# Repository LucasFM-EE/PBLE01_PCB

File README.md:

# PBLE01_PCB

Project designed for the discipline: Project Based Learning 01.

# Requirements
In this project, the board must match these requirements: 

### 1. Power Supply: 
- Support voltage input of 7V to 12V (DC);
- Provide regulated output of 5V;
- Use a LED to indicate that the board is powered.

### 2. Processing:
- Use a PIC18F4550 as a unit of processing and control;
- Use a pin header compatible with the ICSP standard, to program the microcontroller;
- Use a push-button to reset the microcontroller.

### 3. User interaction:
- Have a keyboard, composed by 5 push-buttons;
- Have a LCD display, which its luminosity is controlled by a trimmer;
- Have at least 4 LED's, which are able to signalize different states of the MCU;
- Have a potentiometer, which is used to provide analog data.

### 4. Peripherals
- Use a Real-Time Clock(RTC) - MCP7940;
- Contain 2 pairs of differential analog inputs(4 analog inputs). Each pair must provide a signal between 0V and 3V for the microcontroller; 
- Contain a analog output, made by a PWM signal;
- Contain a pin header that has the reference signal(GND), the power supply signal(VCC) and the microcontroller pins that aren't being used.

### 5. Communication
- Use a USB-Serial converter(MCP2200), to allow serial communication with the board.

# Functional Diagram
The following image shows a functional diagram of the board: 

# Board sections 
The following image shows the board, divided by the sections mentioned above:

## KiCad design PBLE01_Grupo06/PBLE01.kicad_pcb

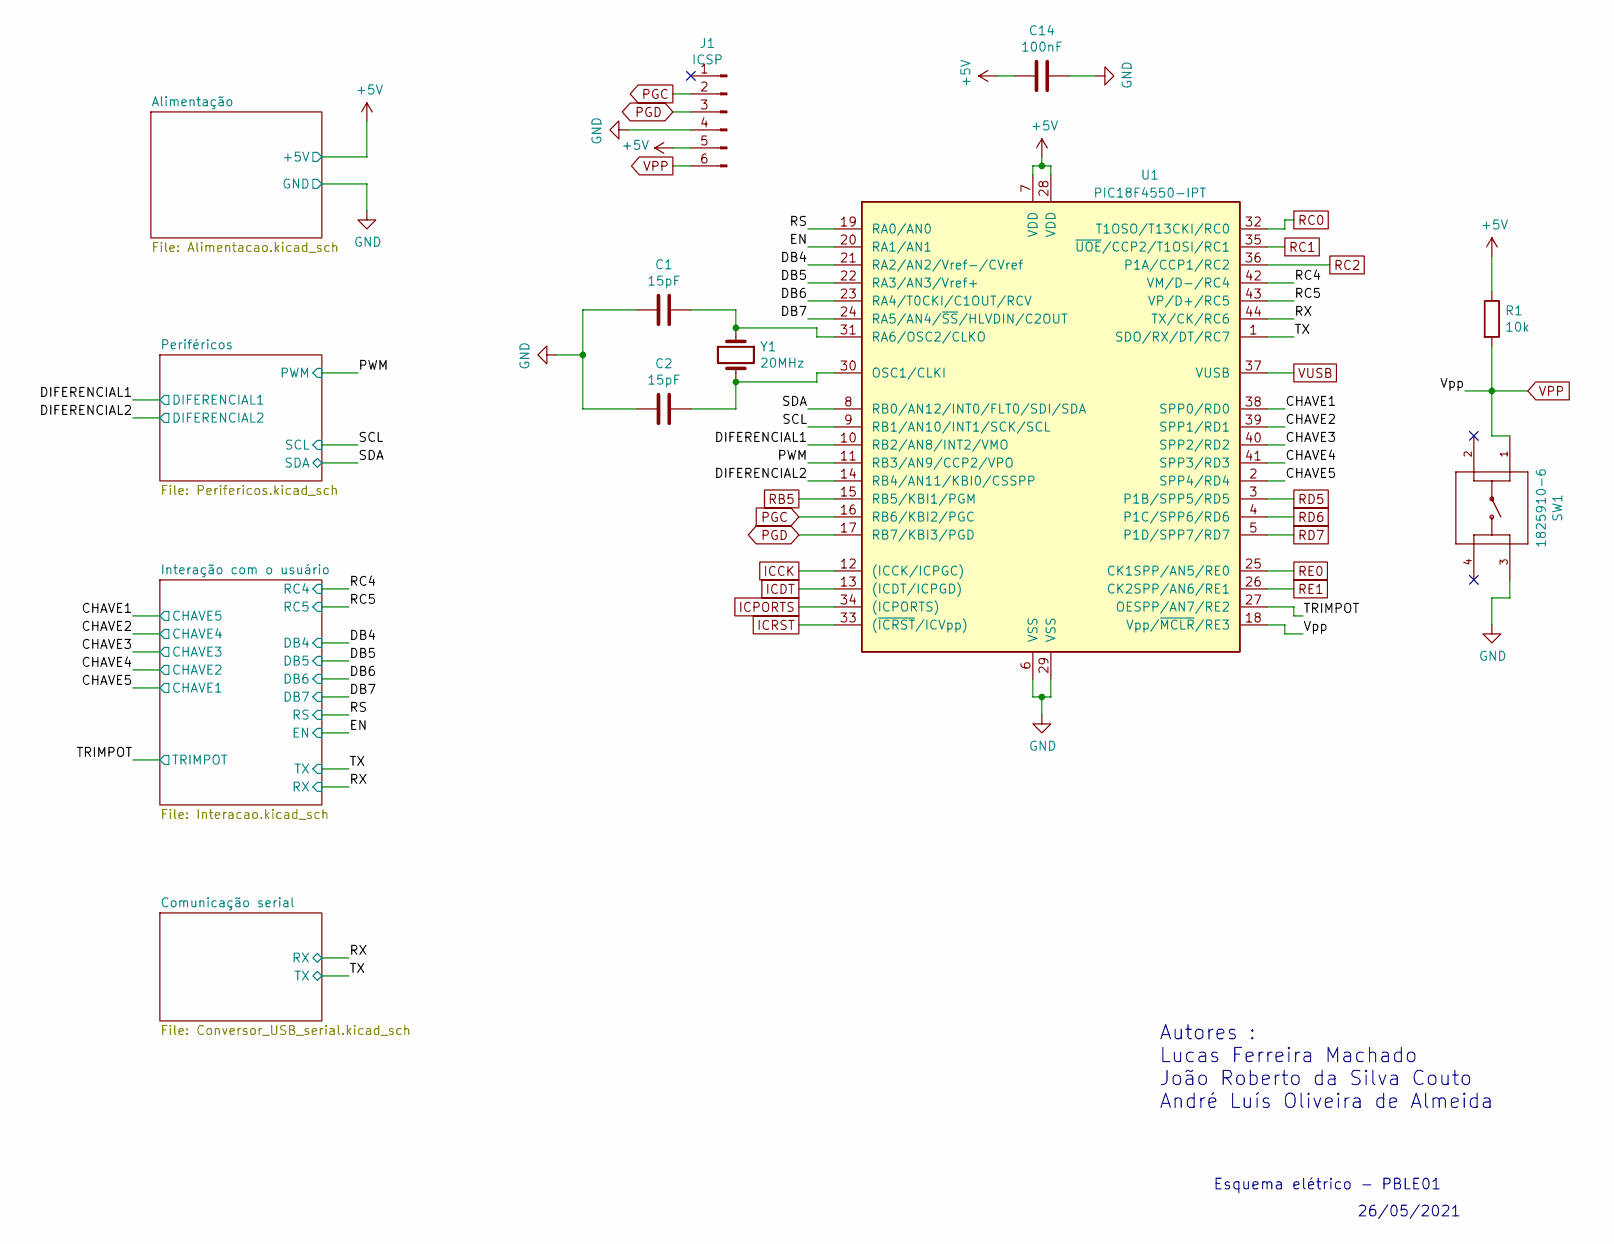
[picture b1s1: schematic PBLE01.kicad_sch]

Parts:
C1, C2: 15pF; C_0805_2012Metric_Pad1.18x1.45mm_HandSolder
C14: 100nF; C_0805_2012Metric_Pad1.18x1.45mm_HandSolder
J1: ICSP; PinHeader_1x06_P2.54mm_Vertical
R1: 10k; R_0805_2012Metric_Pad1.20x1.40mm_HandSolder
SW1: 1825910-6; SW_1825910-6-4
U1: PIC18F4550-IPT; TQFP-44_10x10mm_P0.8mm
Y1: 20MHz; Crystal_HC49-4H_Vertical

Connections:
+5V: C14.1, J1.5, R1.1, U1.7 (VDD), U1.28 (VDD); also elsewhere on the board
/CHAVE1: U1.38 (SPP0/RD0); also elsewhere on the board
/CHAVE2: U1.39 (SPP1/RD1); also elsewhere on the board
/CHAVE3: U1.40 (SPP2/RD2); also elsewhere on the board
/CHAVE4: U1.41 (SPP3/RD3); also elsewhere on the board
/CHAVE5: U1.2 (SPP4/RD4); also elsewhere on the board
/DB4: U1.21 (RA2/AN2/Vref-/CVref); also elsewhere on the board
/DB5: U1.22 (RA3/AN3/Vref+); also elsewhere on the board
/DB6: U1.23 (RA4/T0CKI/C1OUT/RCV); also elsewhere on the board
/DB7: U1.24 (RA5/AN4/~SS/HLVDIN/C2OUT); also elsewhere on the board
/DIFERENCIAL1: U1.10 (RB2/AN8/INT2/VMO); also elsewhere on the board
/DIFERENCIAL2: U1.14 (RB4/AN11/KBI0/CSSPP); also elsewhere on the board
/EN: U1.20 (RA1/AN1); also elsewhere on the board
/PWM: U1.11 (RB3/AN9/CCP2/VPO); also elsewhere on the board
/RC4: U1.42 (VM/D-/RC4); also elsewhere on the board
/RC5: U1.43 (VP/D+/RC5); also elsewhere on the board
/RS: U1.19 (RA0/AN0); also elsewhere on the board
/RX: U1.44 (TX/CK/RC6); also elsewhere on the board
/SCL: U1.9 (RB1/AN10/INT1/SCK/SCL); also elsewhere on the board
/SDA: U1.8 (RB0/AN12/INT0/FLT0/SDI/SDA); also elsewhere on the board
/TRIMPOT: U1.27 (OESPP/AN7/RE2); also elsewhere on the board
/TX: U1.1 (SDO/RX/DT/RC7); also elsewhere on the board
ICCK: U1.12 ((ICCK/ICPGC)); also elsewhere on the board
ICDT: U1.13 ((ICDT/ICPGD)); also elsewhere on the board
ICPORTS: U1.34 ((ICPORTS)); also elsewhere on the board
ICRST: U1.33 ((~ICRST/ICVpp)); also elsewhere on the board
unnamed: C1.2, U1.31 (RA6/OSC2/CLKO), Y1.1
unnamed: C2.2, U1.30 (OSC1/CLKI), Y1.2
PGC: J1.2, U1.16 (RB6/KBI2/PGC)
PGD: J1.3, U1.17 (RB7/KBI3/PGD)
RB5: U1.15 (RB5/KBI1/PGM); also elsewhere on the board
RC0: U1.32 (T1OSO/T13CKI/RC0); also elsewhere on the board
RC1: U1.35 (~UOE/CCP2/T1OSI/RC1); also elsewhere on the board
RC2: U1.36 (P1A/CCP1/RC2); also elsewhere on the board
RD5: U1.3 (P1B/SPP5/RD5); also elsewhere on the board
RD6: U1.4 (P1C/SPP6/RD6); also elsewhere on the board
RD7: U1.5 (P1D/SPP7/RD7); also elsewhere on the board
RE0: U1.25 (CK1SPP/AN5/RE0); also elsewhere on the board
RE1: U1.26 (CK2SPP/AN6/RE1); also elsewhere on the board
VPP: J1.6, R1.2, SW1.1, U1.18 (Vpp/~MCLR/RE3)
VUSB: U1.37 (VUSB); also elsewhere on the board

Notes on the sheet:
Esquema elétrico - PBLE01
Autores : Lucas Ferreira Machado João Roberto da Silva Couto André Luís Oliveira de Almeida
26/05/2021

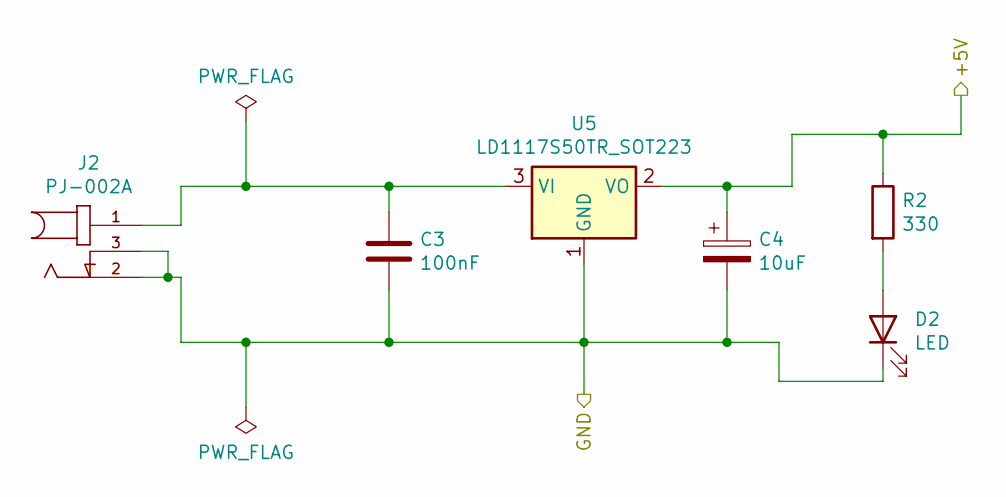
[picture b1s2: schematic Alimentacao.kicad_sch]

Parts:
C3: 100nF; C_0805_2012Metric_Pad1.18x1.45mm_HandSolder
C4: 10uF; CAPPM3216X180N
D2: LED; LTST-C150GKT
J2: PJ-002A; CUI_PJ-002A
R2: 330; R_0805_2012Metric_Pad1.20x1.40mm_HandSolder
U5: LD1117S50TR_SOT223; SOT-223-3_TabPin2

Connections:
+5V: C4.1, R2.1, U5.2 (VO); also elsewhere on the board
unnamed: C3.1, J2.1, U5.3 (VI)
unnamed: D2.2 (A), R2.2

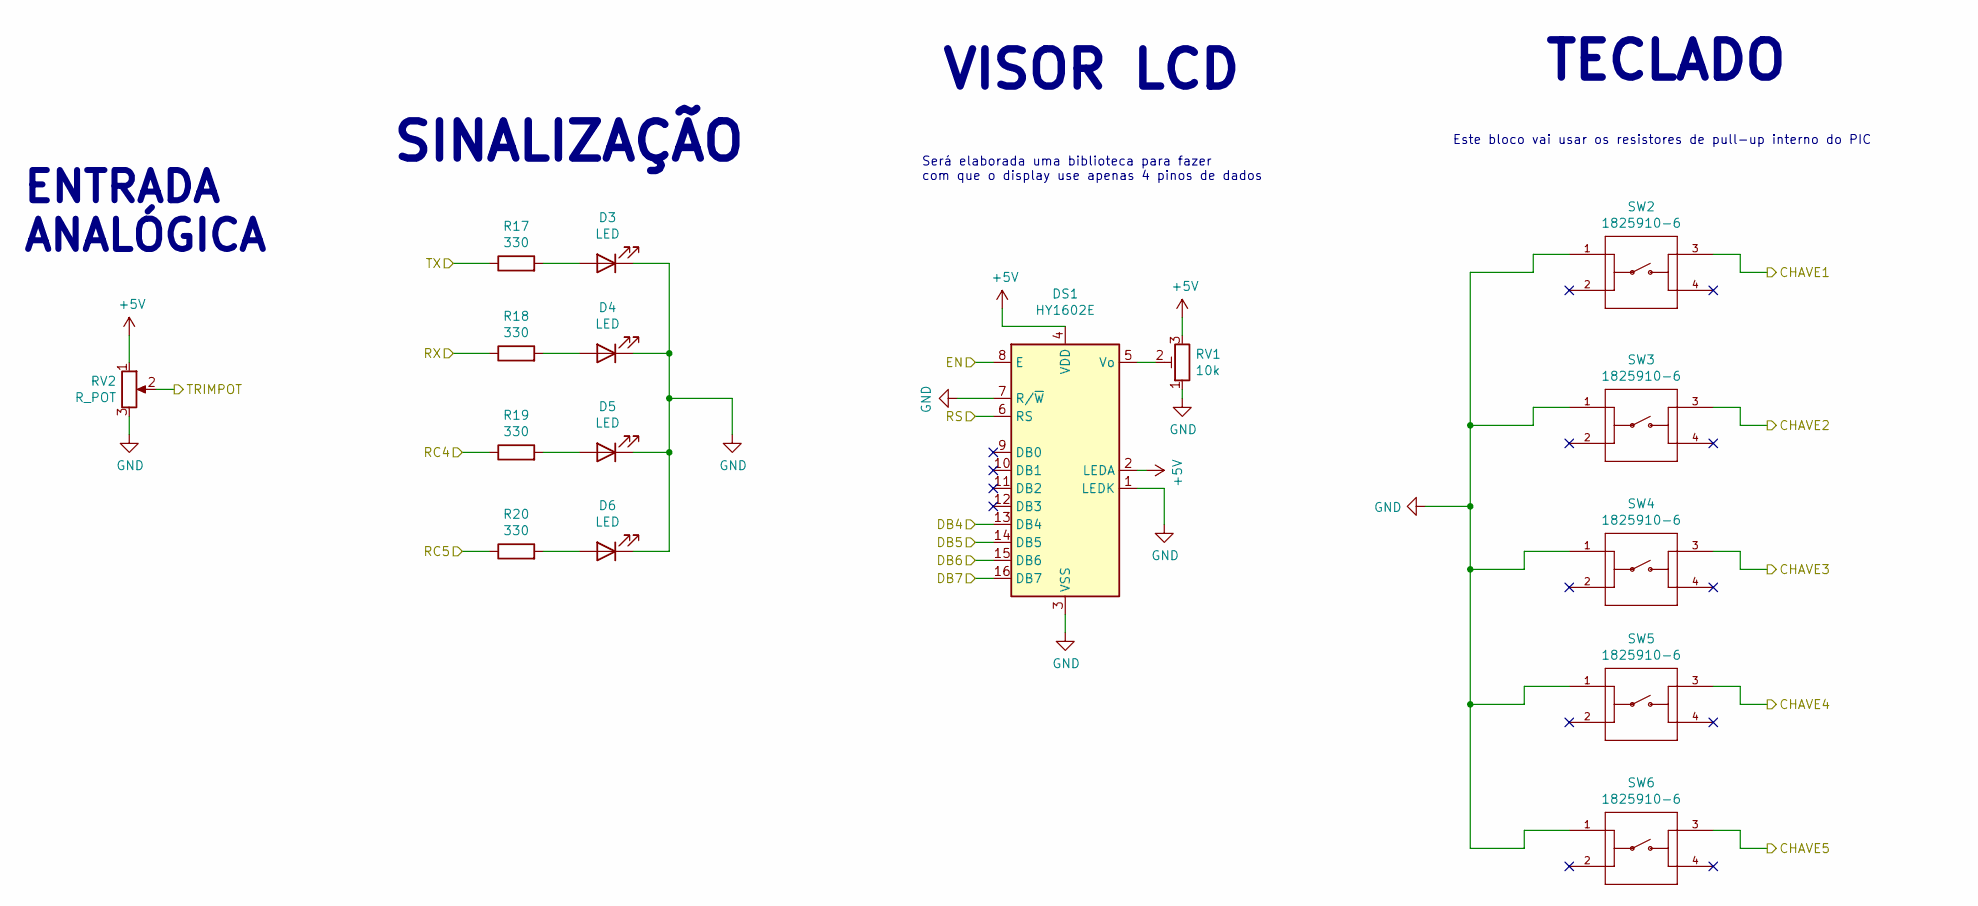
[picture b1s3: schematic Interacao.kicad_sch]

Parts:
D3, D4, D5, D6: LED; LTST-C150GKT
DS1: HY1602E
R17, R18, R19, R20: 330; R_0805_2012Metric_Pad1.20x1.40mm_HandSolder
RV1: 10k; Potentiometer_Bourns_3296W_Vertical
RV2: R_POT; P160KN0QC15B100K
SW2, SW3, SW4, SW5, SW6: 1825910-6; SW_1825910-6-4

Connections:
+5V: DS1.2 (LEDA), DS1.4 (VDD), RV1.3, RV2.1; also elsewhere on the board
/CHAVE1: SW6.3; also elsewhere on the board
/CHAVE2: SW5.3; also elsewhere on the board
/CHAVE3: SW4.3; also elsewhere on the board
/CHAVE4: SW3.3; also elsewhere on the board
/CHAVE5: SW2.3; also elsewhere on the board
/DB4: DS1.13 (DB4); also elsewhere on the board
/DB5: DS1.14 (DB5); also elsewhere on the board
/DB6: DS1.15 (DB6); also elsewhere on the board
/DB7: DS1.16 (DB7); also elsewhere on the board
/EN: DS1.8 (E); also elsewhere on the board
/RC4: R19.1; also elsewhere on the board
/RC5: R20.1; also elsewhere on the board
/RS: DS1.6 (RS); also elsewhere on the board
/RX: R18.1; also elsewhere on the board
/TRIMPOT: RV2.2; also elsewhere on the board
/TX: R17.1; also elsewhere on the board
unnamed: D3.2 (A), R17.2
unnamed: D4.2 (A), R18.2
unnamed: D5.2 (A), R19.2
unnamed: D6.2 (A), R20.2
unnamed: DS1.5 (Vo), RV1.2

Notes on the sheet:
Será elaborada uma biblioteca para fazer com que o display use apenas 4 pinos de dados
ENTRADA ANALÓGICA
VISOR LCD
TECLADO
Este bloco vai usar os resistores de pull-up interno do PIC
SINALIZAÇÃO

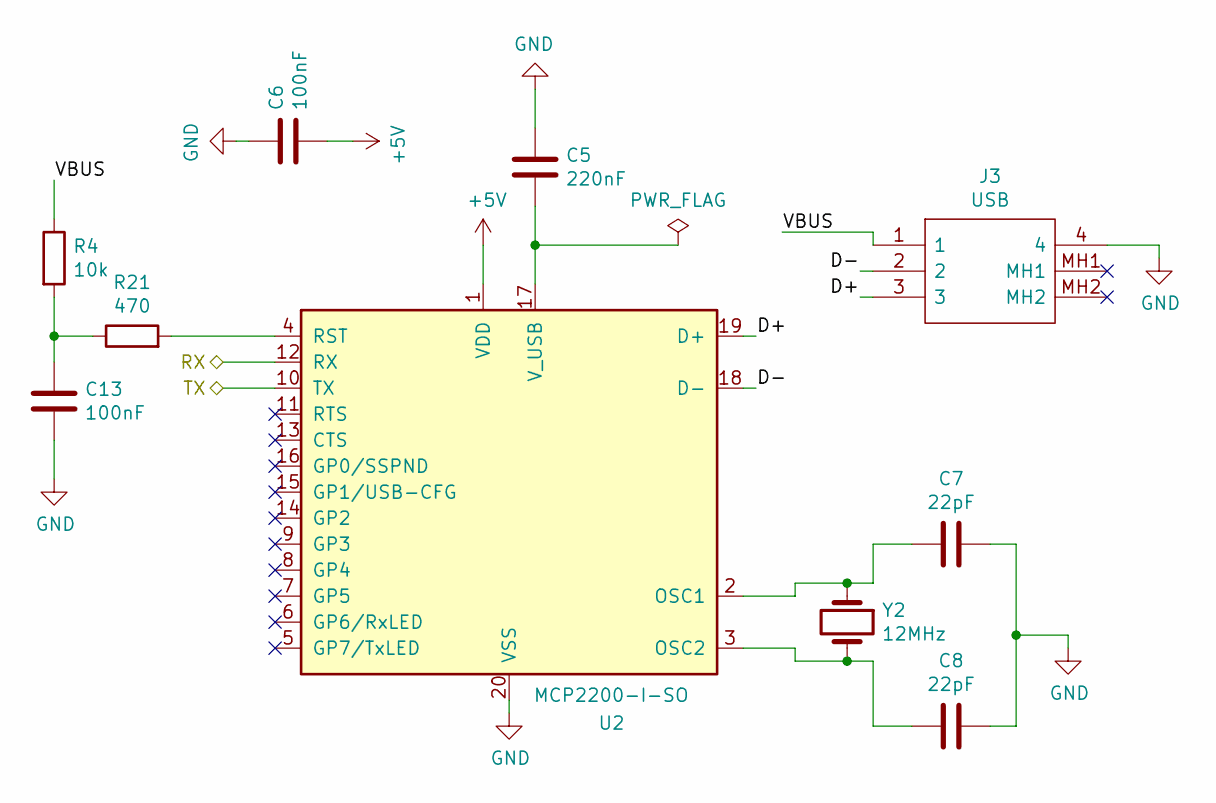
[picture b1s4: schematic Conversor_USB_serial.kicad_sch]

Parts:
C5: 220nF; C_0805_2012Metric_Pad1.18x1.45mm_HandSolder
C6, C13: 100nF; C_0805_2012Metric_Pad1.18x1.45mm_HandSolder
C7, C8: 22pF; C_0805_2012Metric_Pad1.18x1.45mm_HandSolder
J3: USB; 8974300490000000; Mouser Part Number 575-8974349
R4: 10k; R_0805_2012Metric_Pad1.20x1.40mm_HandSolder
R21: 470; R_0805_2012Metric_Pad1.20x1.40mm_HandSolder
U2: MCP2200-I-SO; SOIC-20W_7.5x12.8mm_P1.27mm
Y2: 12MHz; Crystal_HC49-4H_Vertical

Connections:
+5V: C6.2, U2.1 (VDD); also elsewhere on the board
/Comunicação serial /VBUS: J3.1, R4.1
/RX: U2.12 (RX); also elsewhere on the board
/TX: U2.10 (TX); also elsewhere on the board
unnamed: C5.2, U2.17 (V_USB)
unnamed: C7.2, U2.2 (OSC1), Y2.1
unnamed: C8.1, U2.3 (OSC2), Y2.2
unnamed: C13.1, R4.2, R21.1
unnamed: J3.2, U2.18 (D-)
unnamed: J3.3, U2.19 (D+)
unnamed: R21.2, U2.4 (RST)

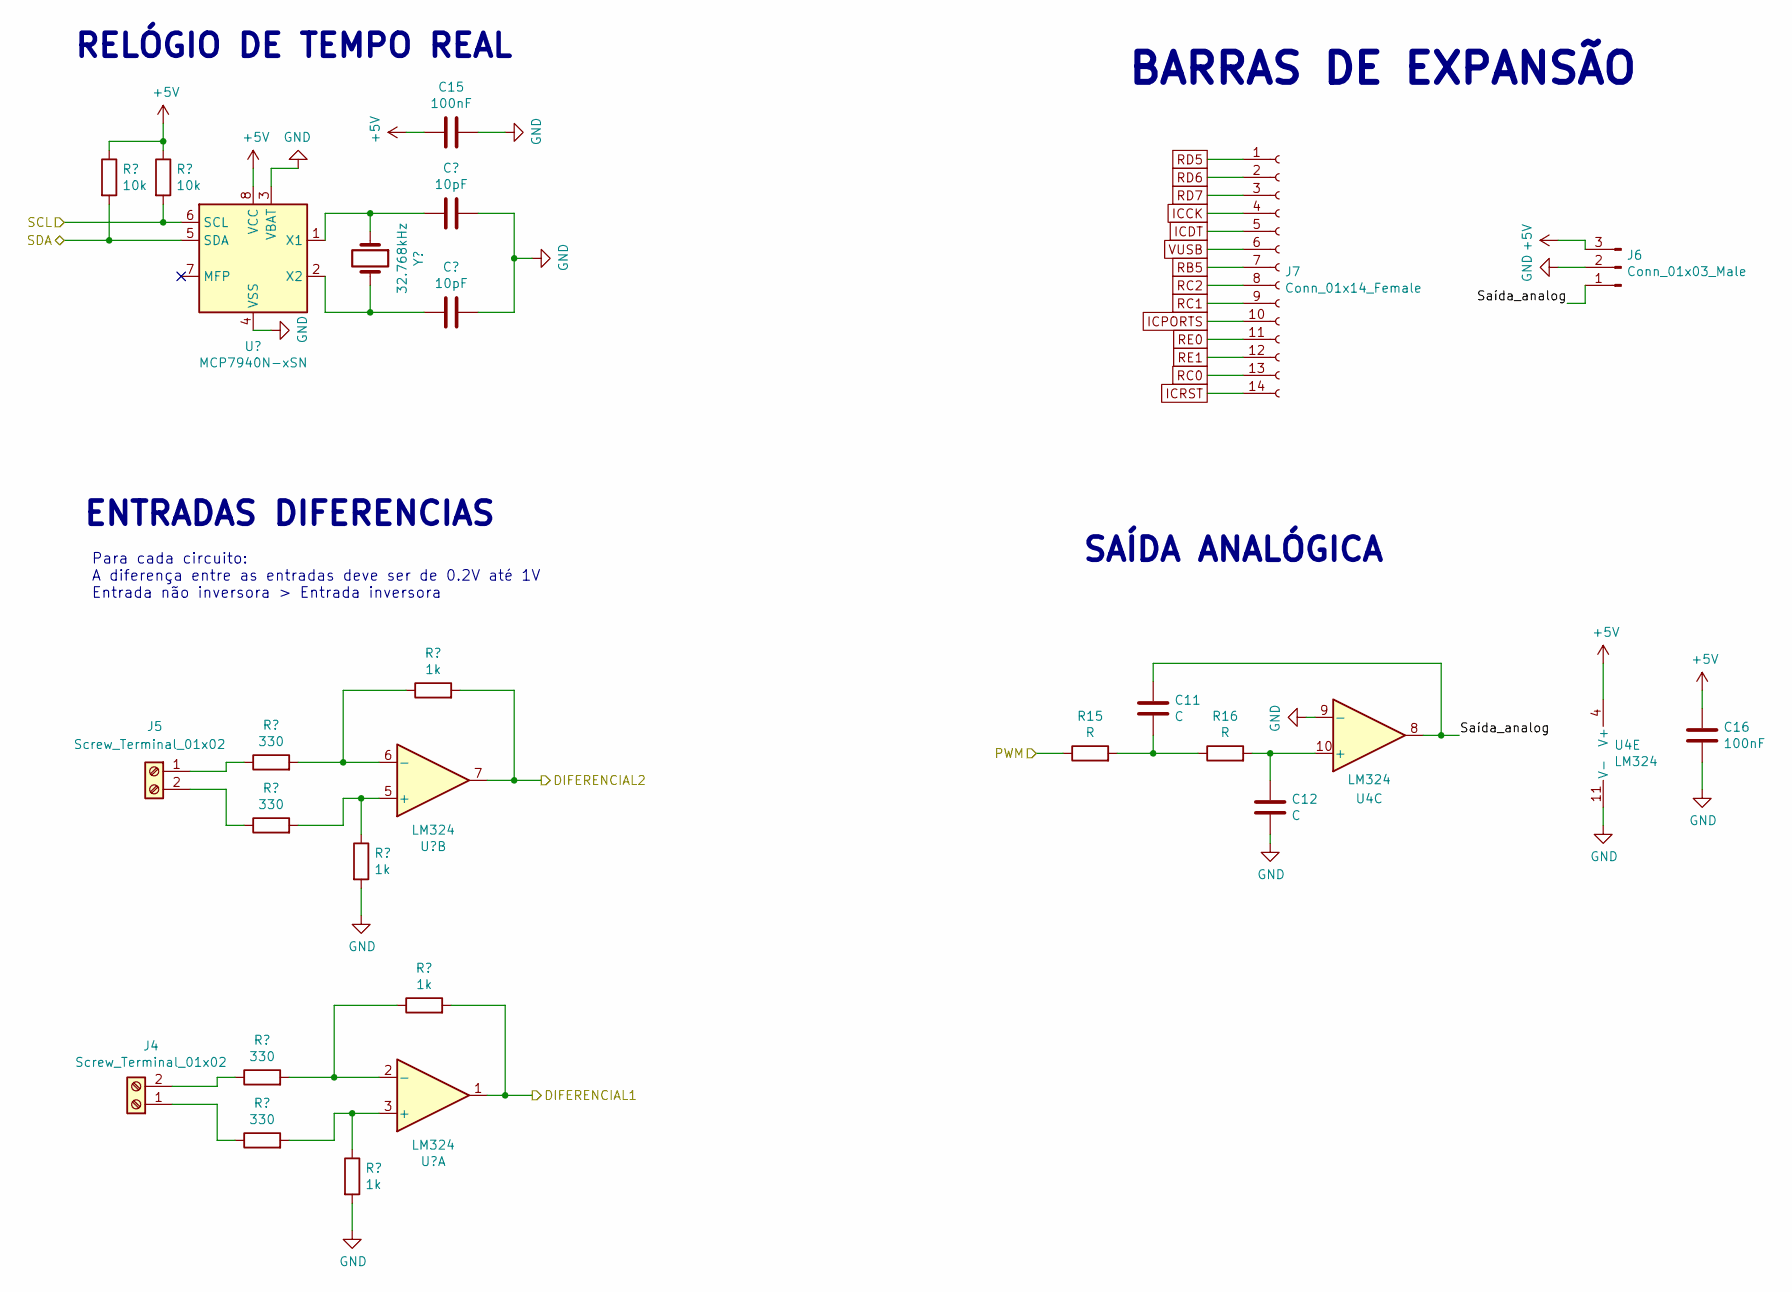
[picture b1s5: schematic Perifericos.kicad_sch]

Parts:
C9, C10: 10pF; C_0805_2012Metric_Pad1.18x1.45mm_HandSolder
C11, C12: C; C_0805_2012Metric_Pad1.18x1.45mm_HandSolder
C15, C16: 100nF; C_0805_2012Metric_Pad1.18x1.45mm_HandSolder
J4, J5: Screw_Terminal_01x02; TerminalBlock_MetzConnect_Type011_RT05502HBWC_1x02_P5.00mm_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
J6: Conn_01x03_Male; PinHeader_1x03_P2.54mm_Vertical
J7: Conn_01x14_Female; PinSocket_1x14_P2.54mm_Vertical
R5, R6: 10k; R_0805_2012Metric_Pad1.20x1.40mm_HandSolder
R7, R8, R11, R12: 330; R_0805_2012Metric_Pad1.20x1.40mm_HandSolder
R9, R10, R13, R14: 1k; R_0805_2012Metric_Pad1.20x1.40mm_HandSolder
R15, R16: R; R_0805_2012Metric_Pad1.20x1.40mm_HandSolder
U3: MCP7940N-xSN; SOIC127P600X175-8N
U4: LM324; SOIC127P600X175-14N
Y3: 32.768kHz; XTAL_AB38T-32.768KHZ

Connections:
+5V: C15.1, C16.1, J6.3, R5.1, R6.1, U3.8 (VCC), U4.4 (V+); also elsewhere on the board
/DIFERENCIAL1: R9.2, U4.1; also elsewhere on the board
/DIFERENCIAL2: R13.2, U4.7; also elsewhere on the board
/PWM: R15.1; also elsewhere on the board
/SCL: R6.2, U3.6 (SCL); also elsewhere on the board
/SDA: R5.2, U3.5 (SDA); also elsewhere on the board
ICCK: J7.4; also elsewhere on the board
ICDT: J7.5; also elsewhere on the board
ICPORTS: J7.10; also elsewhere on the board
ICRST: J7.14; also elsewhere on the board
unnamed: C9.2, U3.1 (X1), Y3.1
unnamed: C10.1, U3.2 (X2), Y3.2
unnamed: C11.2, R15.2, R16.1
unnamed: C12.1, R16.2, U4.10 (+)
unnamed: J4.1, R8.1
unnamed: J4.2, R7.1
unnamed: J5.1, R11.1
unnamed: J5.2, R12.1
unnamed: R7.2, R9.1, U4.2 (-)
unnamed: R8.2, R10.1, U4.3 (+)
unnamed: R11.2, R13.1, U4.6 (-)
unnamed: R12.2, R14.1, U4.5 (+)
RB5: J7.7; also elsewhere on the board
RC0: J7.13; also elsewhere on the board
RC1: J7.9; also elsewhere on the board
RC2: J7.8; also elsewhere on the board
RD5: J7.1; also elsewhere on the board
RD6: J7.2; also elsewhere on the board
RD7: J7.3; also elsewhere on the board
RE0: J7.11; also elsewhere on the board
RE1: J7.12; also elsewhere on the board
VUSB: J7.6; also elsewhere on the board

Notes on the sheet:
RELÓGIO DE TEMPO REAL
ENTRADAS DIFERENCIAS
BARRAS DE EXPANSÃO
SAÍDA ANALÓGICA
Para cada circuito: A diferença entre as entradas deve ser de 0.2V até 1V Entrada não inversora > Entrada inversora

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
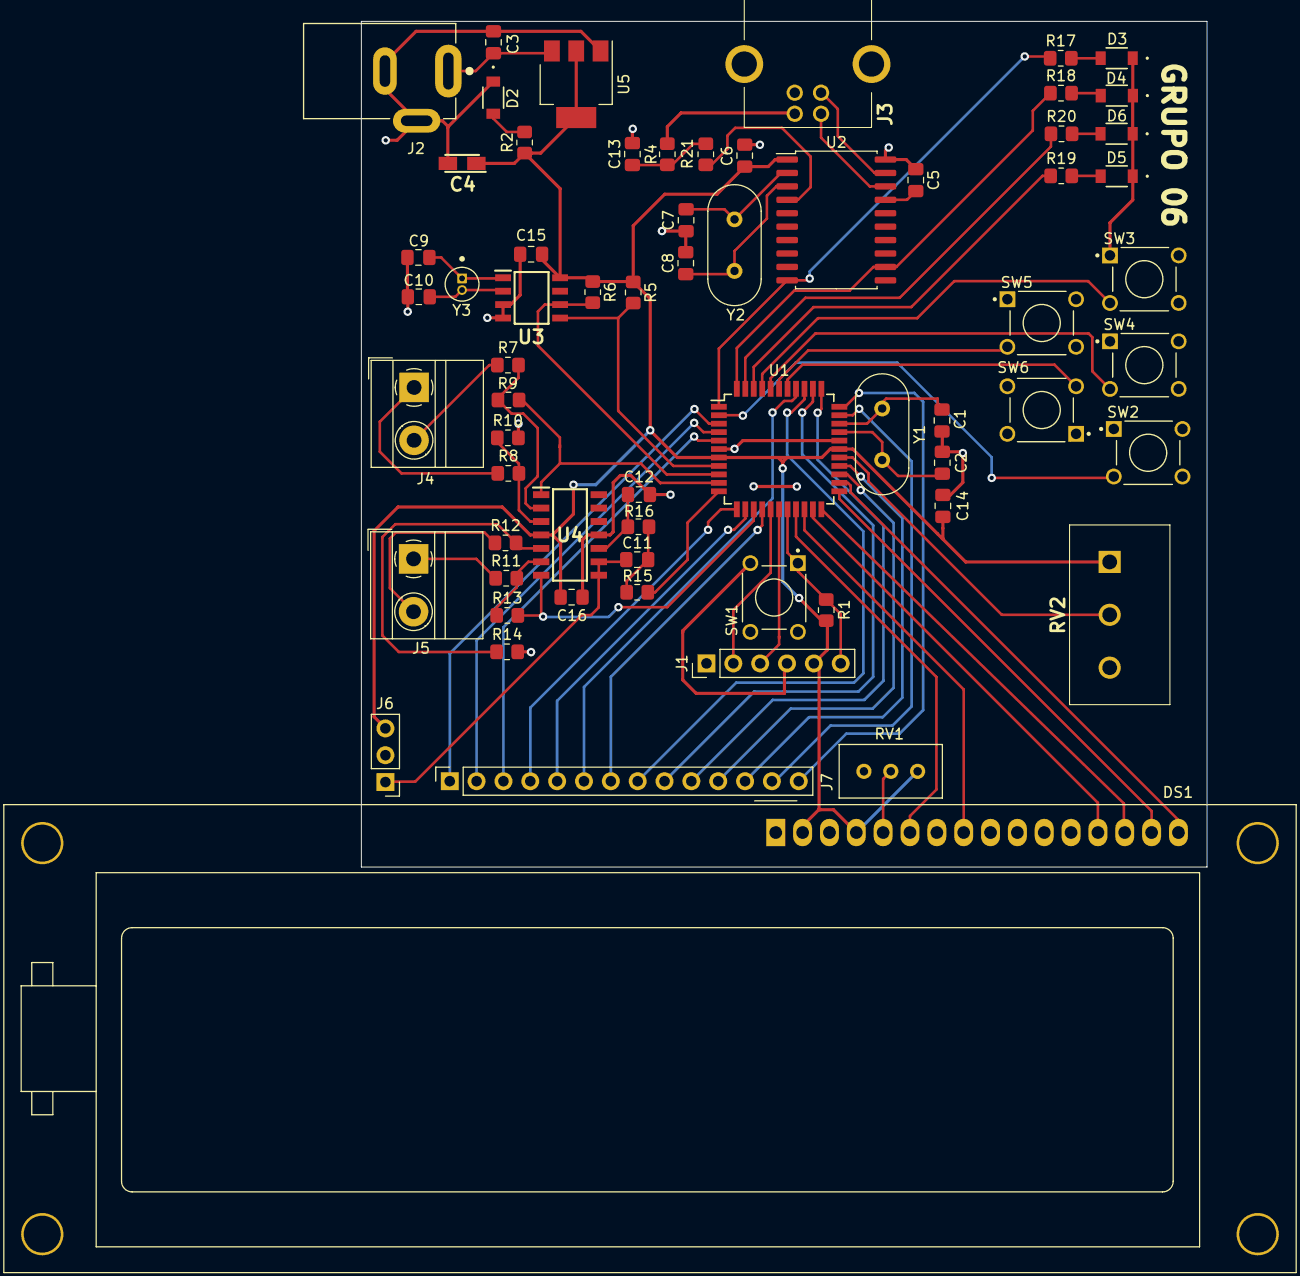
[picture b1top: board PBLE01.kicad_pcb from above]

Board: 2 copper layers, 80.0 x 80.0 mm, 65 parts (0 on the bottom side), 70 nets.

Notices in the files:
parts and their libraries:
Copyright 2016 Accelerated Designs. All rights reserved.
